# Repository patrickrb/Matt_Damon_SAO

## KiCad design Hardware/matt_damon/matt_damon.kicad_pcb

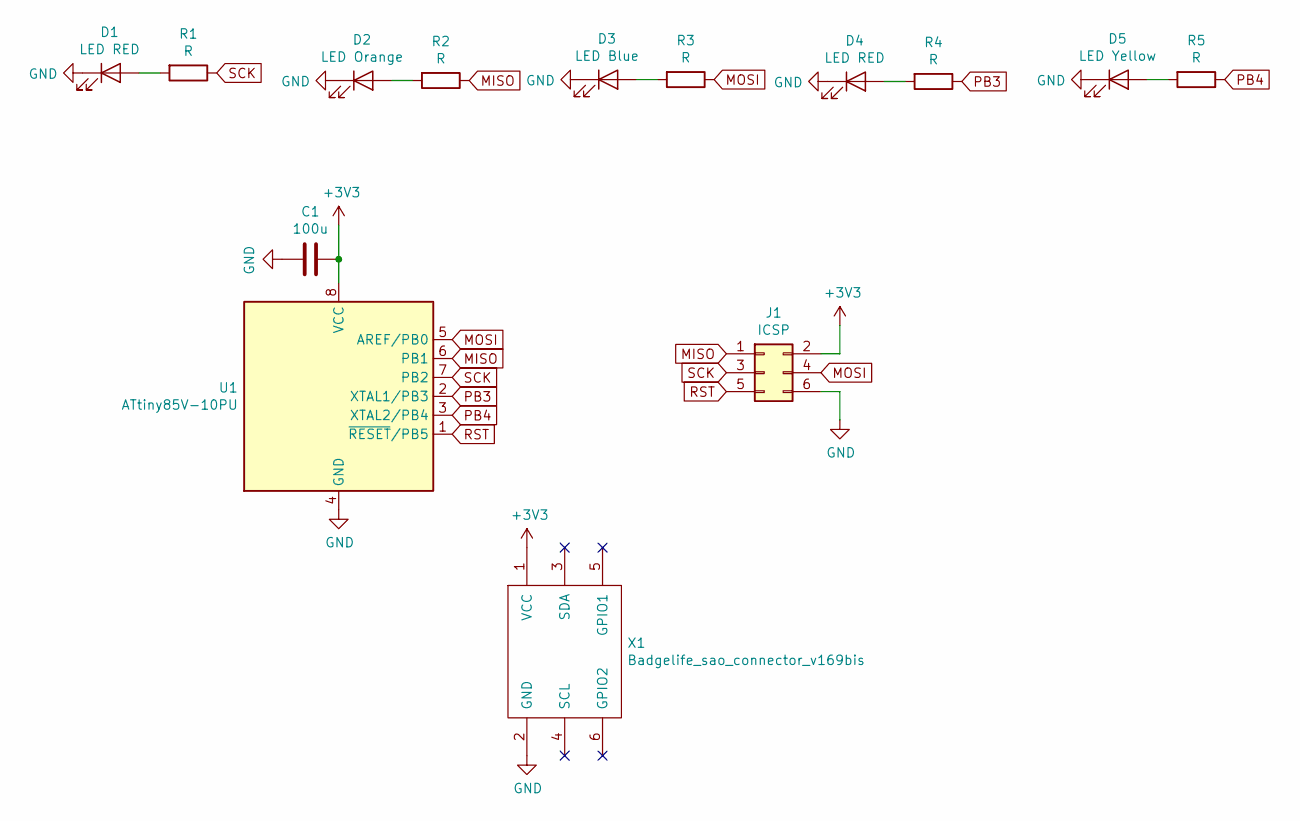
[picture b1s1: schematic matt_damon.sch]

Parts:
C1: 100u; C_0805_2012Metric
D1, D4: LED RED; LED_1206_3216Metric
D2: LED Orange; LED_1206_3216Metric
D3: LED Blue; LED_1206_3216Metric
D5: LED Yellow; LED_1206_3216Metric
J1: ICSP; PinHeader_2x03_P2.54mm_Vertical_SMD
R1, R2, R3, R4, R5: R; R_0805_2012Metric_Pad1.15x1.40mm_HandSolder
U1: ATtiny85V-10PU; SOIJ-8_5.3x5.3mm_P1.27mm
X1: Badgelife_sao_connector_v169bis; Badgelife-SAOv169-SAO-2x3

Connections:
+3V3: C1.1, J1.2, U1.8 (VCC), X1.1 (VCC)
GND: C1.2, D1.1 (K), D2.1 (K), D3.1 (K), D4.1 (K), D5.1 (K), J1.6, U1.4 (GND), X1.2 (GND)
MISO: J1.1, R2.1, U1.6 (PB1)
MOSI: J1.4, R3.1, U1.5 (AREF/PB0)
unnamed: D1.2 (A), R1.2
unnamed: D2.2 (A), R2.2
unnamed: D3.2 (A), R3.2
unnamed: D4.2 (A), R4.2
unnamed: D5.2 (A), R5.2
PB3: R4.1, U1.2 (XTAL1/PB3)
PB4: R5.1, U1.3 (XTAL2/PB4)
RST: J1.5, U1.1 (~RESET~/PB5)
SCK: J1.3, R1.1, U1.7 (PB2)

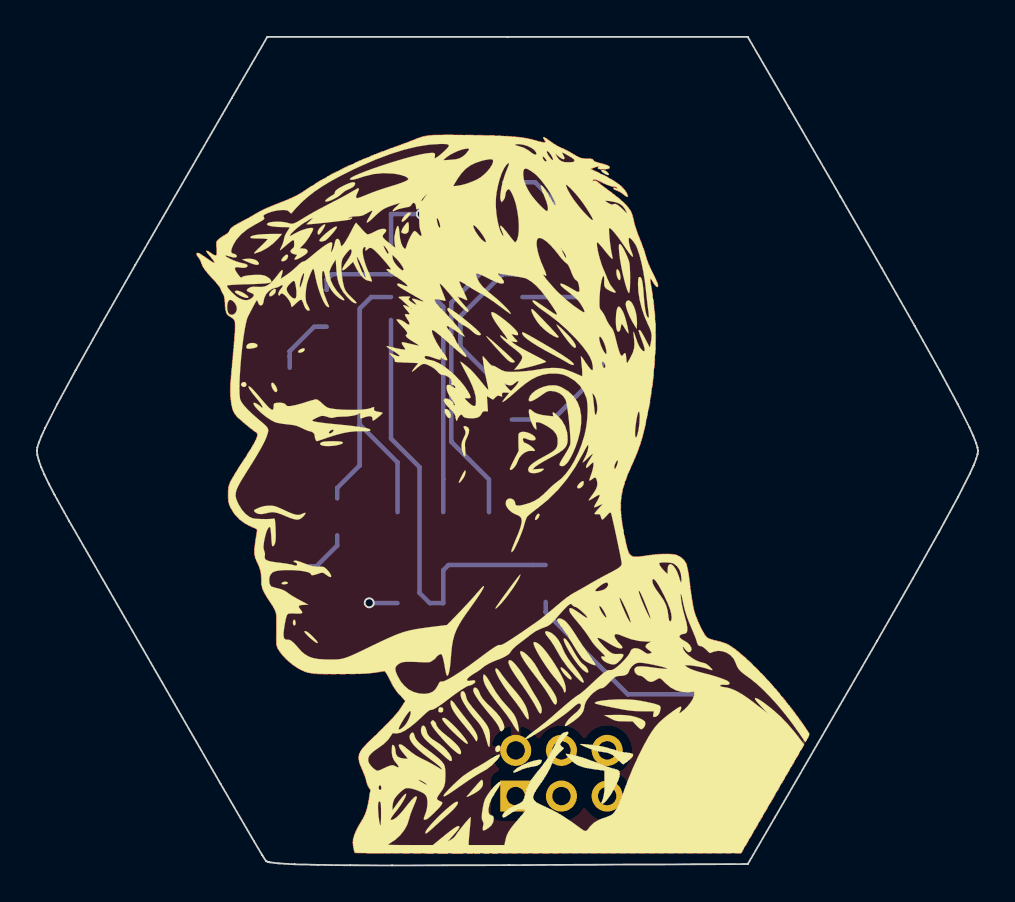
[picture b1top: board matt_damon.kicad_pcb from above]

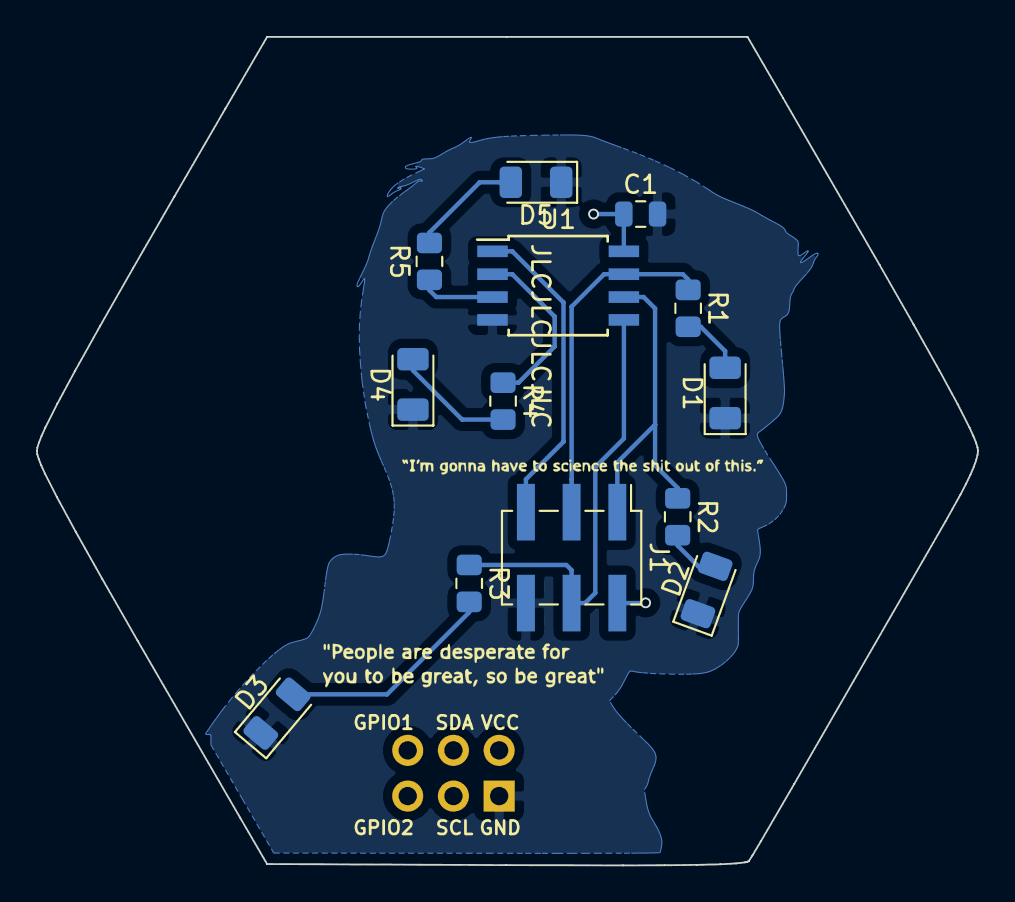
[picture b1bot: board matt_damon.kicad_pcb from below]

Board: 2 copper layers, 52.3 x 46.0 mm, 14 parts (13 on the bottom side), 13 nets.

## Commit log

2020-07-31 first
2020-08-07 final code
2020-08-13 matt damon!
